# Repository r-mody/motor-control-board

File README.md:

# motor-control-board
Kicad project to create a simple DC Brushed motor control board compatible with the Nucelo64 STM32F0.

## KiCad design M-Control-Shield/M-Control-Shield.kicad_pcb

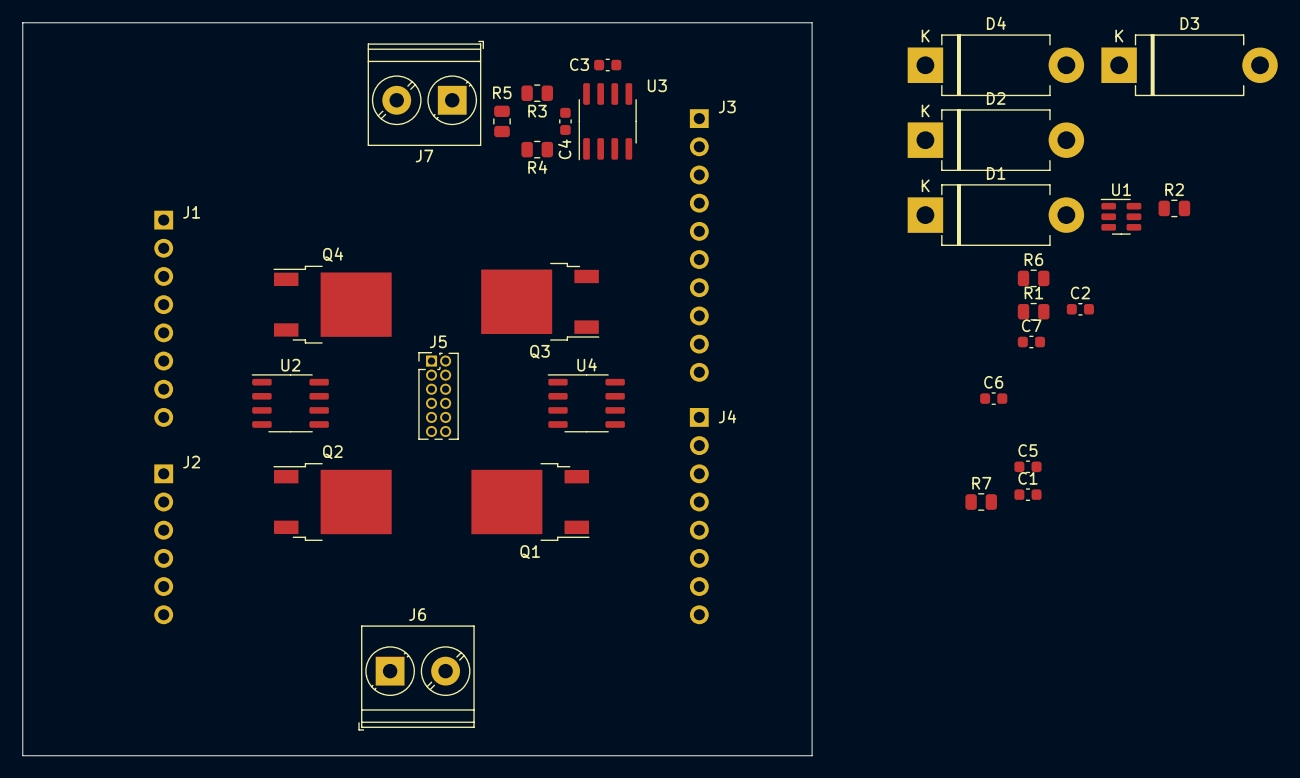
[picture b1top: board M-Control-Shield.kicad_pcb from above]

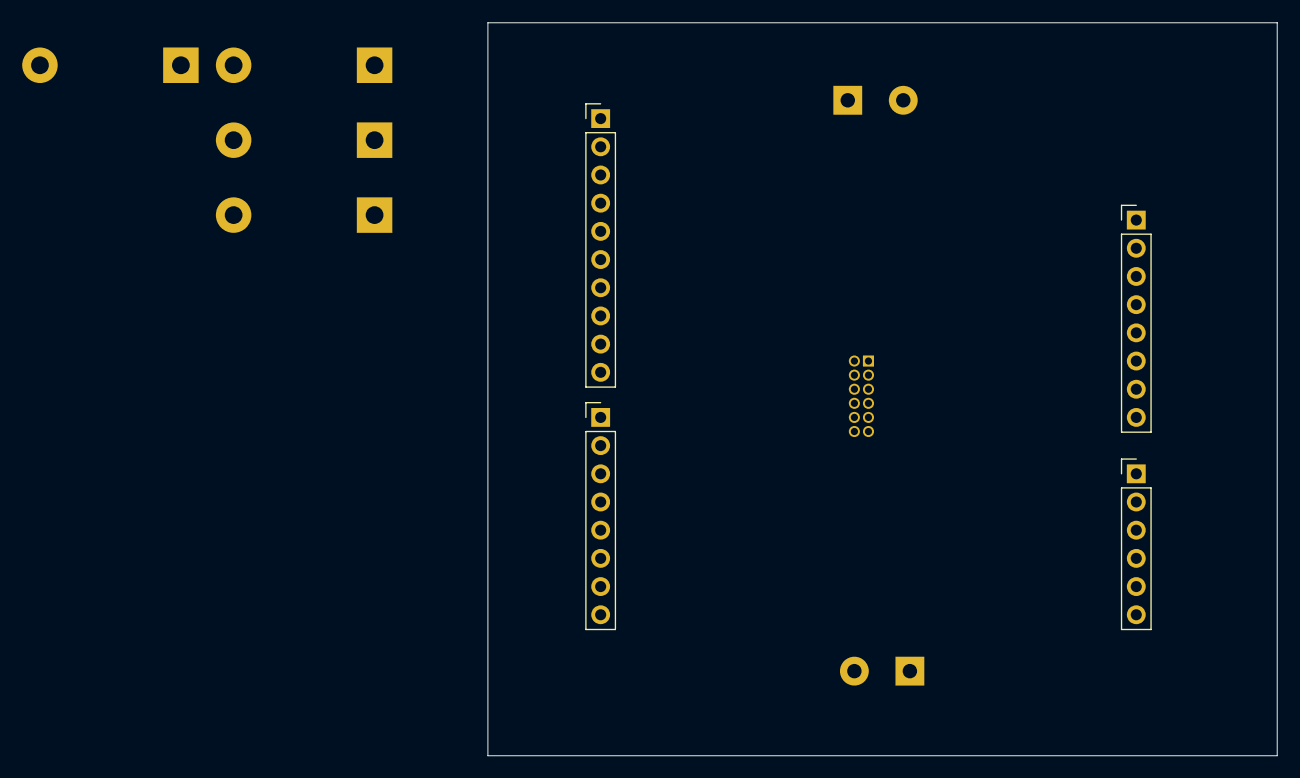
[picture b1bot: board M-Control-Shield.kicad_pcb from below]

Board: 2 copper layers, 71.1 x 66.0 mm, 33 parts (4 on the bottom side), 17 nets, no tracks yet.

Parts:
C1, C2, C3, C4, C5, C6, C7: C; C_0603_1608Metric
D1, D2, D3, D4: SB10150; D_DO-201AD_P12.70mm_Horizontal
J1, J4: Conn_01x08; PinHeader_1x08_P2.54mm_Vertical
J2: Conn_01x06; PinHeader_1x06_P2.54mm_Vertical
J3: Conn_01x10; PinHeader_1x10_P2.54mm_Vertical
J5: Conn_02x06_Row_Letter_First; PinHeader_2x06_P1.27mm_Vertical
J6, J7: Screw_Terminal_01x02; TerminalBlock_Phoenix_PT-1,5-2-5.0-H_1x02_P5.00mm_Horizontal
Q1, Q3: AOD413A; TO-252-2
Q2, Q4: AOD454A; TO-252-2
R1, R2, R3, R4, R5, R6, R7: R; R_0805_2012Metric
U1: SN74LVC1G374; SOT-23-6
U2, U4: MAX17601; SO-8_3.9x4.9mm_P1.27mm
U3: INA240A4D; SOIC-8_3.9x4.9mm_P1.27mm

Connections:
+3.3V: C1.1, C3.1, J1.4, U1.5 (VCC), U3.6 (V+)
+12V: C2.1, C5.1, C6.1, C7.1, J7.2, R3.2, R5.2, U2.5 (VDD), U4.5 (VDD)
/A0: J2.1, J2.2, U3.5
/COMP1_OUT: J3.6, U1.3 (D)
/D2: J4.6, U2.2 (INA), U4.4 (INB)
/D7: J4.1, U2.4 (INB), U4.2 (INA)
/D11: J3.7, U1.1 (CLK)
GND: C1.2, C2.2, C3.2, C5.2, C6.2, C7.2, D2.2 (A), D4.2 (A), J1.6, J1.7, J3.4, J7.1, Q2.3 (S), Q4.3 (S), R1.1, R6.1, U1.2 (GND), U2.3 (GND), U3.2 (GND), U3.3 (REF2), U3.4 (GND), U3.7 (REF1), U4.3 (GND)
unnamed: C4.1, R3.1, U3.8 (+)
unnamed: C4.2, R4.1, U3.1 (-)
unnamed: D1.1 (K), D3.1 (K), Q1.3 (S), Q3.3 (S), R2.2, R4.2, R5.1, R7.2
unnamed: D1.2 (A), D2.1 (K), J6.1, Q1.2 (D), Q2.2 (D)
unnamed: D3.2 (A), D4.1 (K), J6.2, Q3.2 (D), Q4.2 (D)
unnamed: Q1.1 (G), R2.1
unnamed: Q2.1 (G), R1.2, U2.7 (OUTA)
unnamed: Q3.1 (G), R7.1
unnamed: Q4.1 (G), R6.2, U4.7 (OUTA)

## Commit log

2022-07-19 KiCad base files
2022-07-19 Replacing original files with Nucleo64 Arduino Shield template
2022-07-19 Added full bridge and low side current measurement amplifier
2022-08-02 Changed HS FETs to PMOS
2022-08-05 Added flyback diodes
2023-11-01 Removed gate drives and 555
2023-11-07 Adding MAX17602 gate driver
2023-11-09 Adding cubemx .ioc file for setting up mcu
2023-11-09 Adding connections for PWM and enables
2023-11-16 Adding gitignore file
2023-11-26 Added safety latch for shoot through
2023-11-26 Annotated and imported to pcb
2023-12-06 Placement of FETs, connectors, and current measurement circuit
